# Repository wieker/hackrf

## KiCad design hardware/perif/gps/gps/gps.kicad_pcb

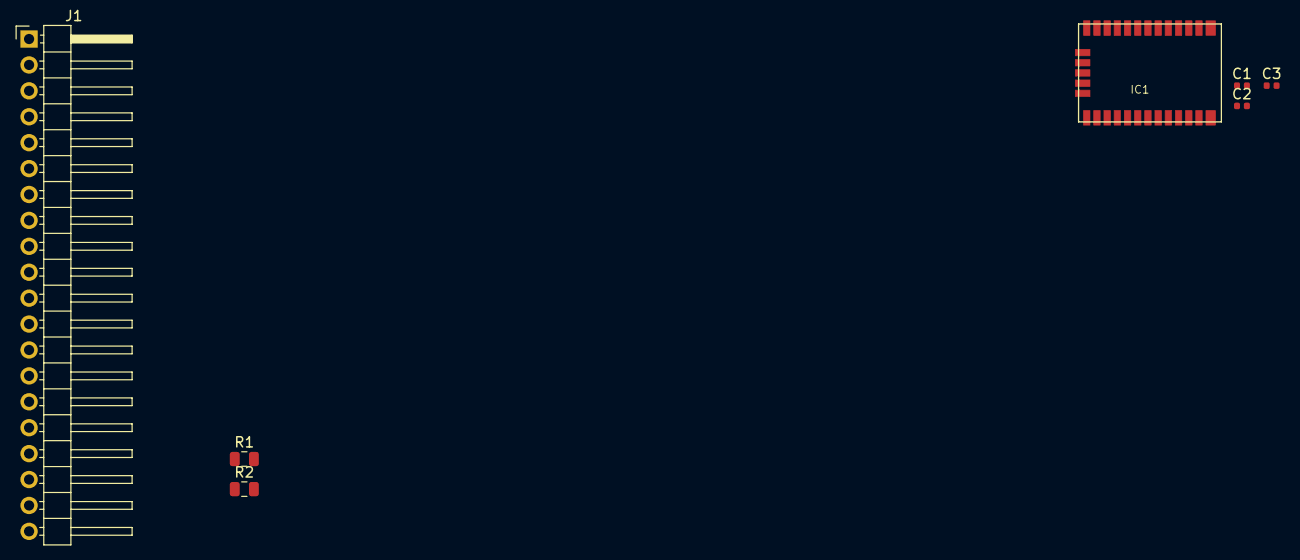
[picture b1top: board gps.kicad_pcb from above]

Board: 2 copper layers, 7 parts (0 on the bottom side), 7 nets, no tracks yet.

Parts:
C1, C2, C3: C; C_0402_1005Metric
IC1: CAM-M8Q
J1: Conn_01x20_Male; PinHeader_1x20_P2.54mm_Horizontal
R1, R2: 200; R_0805_2012Metric

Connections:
+3V3: C1.1, C2.1, C3.1, IC1.1, IC1.8, IC1.9, J1.19
GND: C1.2, C2.2, C3.2, IC1.4, IC1.5, IC1.10, IC1.11, IC1.12, IC1.13, IC1.14, IC1.15, IC1.18, IC1.19, IC1.21, IC1.22, IC1.27, IC1.31, J1.1, J1.4, J1.8, J1.15, J1.18, J1.20
unnamed: IC1.16, IC1.17
unnamed: IC1.25, R1.2
unnamed: IC1.26, R2.2
master_rx: J1.17, R1.1
master_tx: J1.16, R2.1

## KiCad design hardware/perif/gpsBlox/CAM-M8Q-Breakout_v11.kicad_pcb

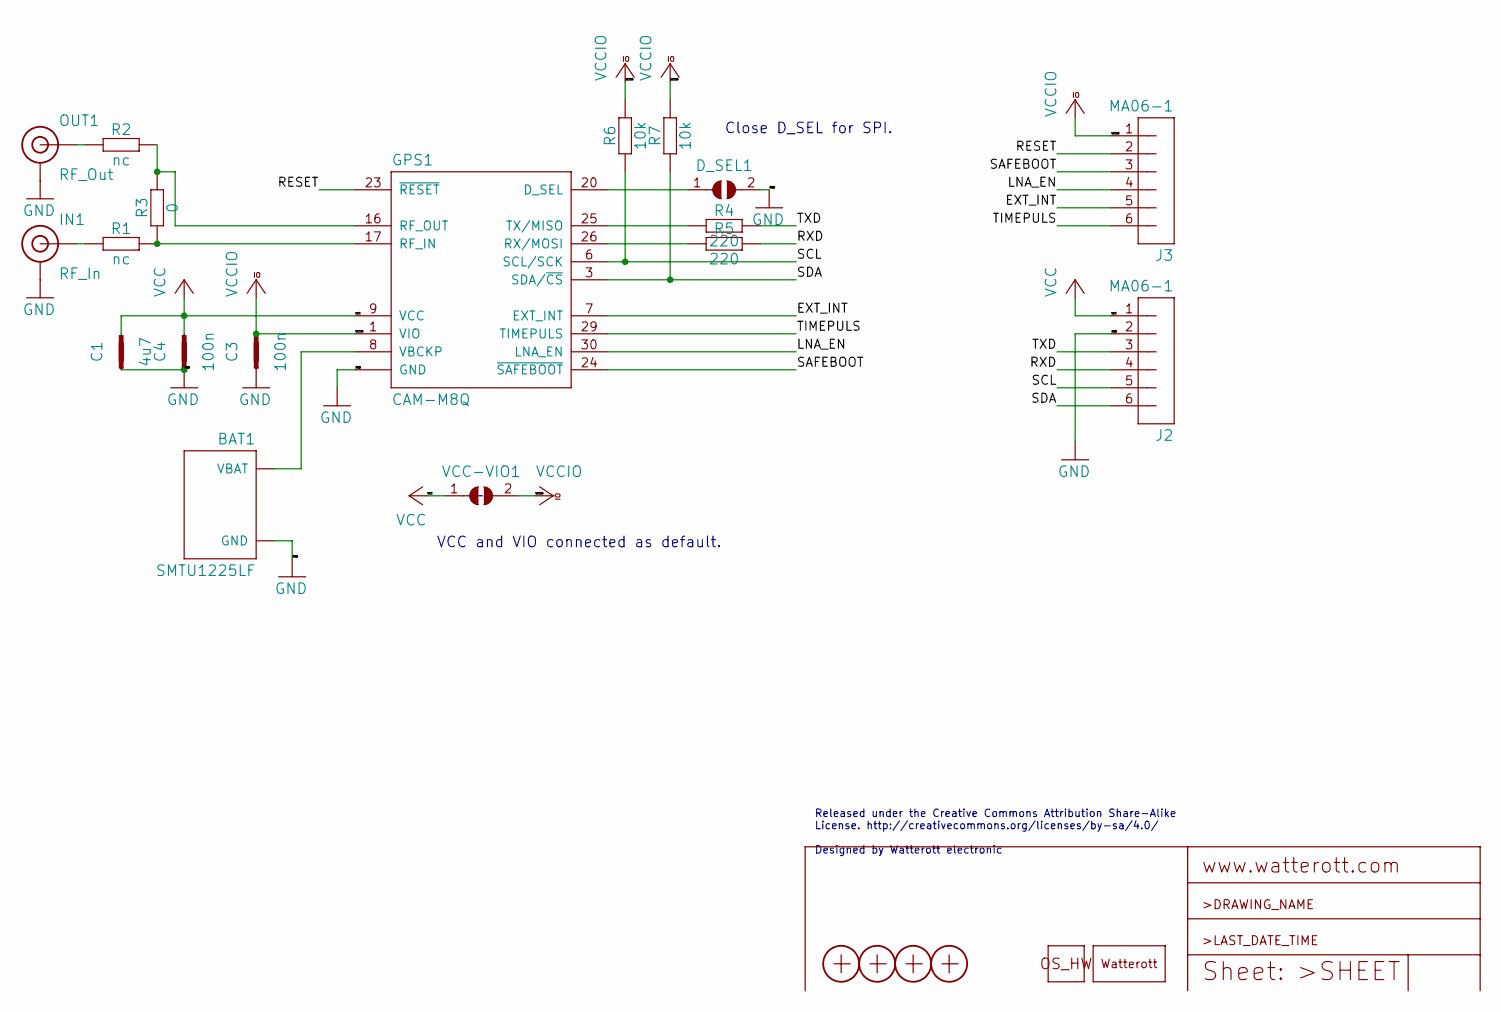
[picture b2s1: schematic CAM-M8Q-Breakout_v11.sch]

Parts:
BAT1: SMTU1225LF; BAT-SMTU1225LF
C1: 4u7; C0402
C3, C4: 100n; C0402
D_SEL1: JUMPER2-0603-NC; JUMPER2-0603_NC
GPS1: CAM-M8Q
IN1: RF_In; U.FL
J2, J3: MA06-1
LOGO3: LOGO_SPARK-4; SPARK_4MM
LOGO4: LOGO_OSHW-2; OSHW_2MM
OUT1: RF_Out; U.FL
R1, R2: nc; C0402
R3: 0; C0402
R4, R5: 220; C0402
R6, R7: 10k; C0402
VCC-VIO1: JUMPER2-0603-NC; JUMPER2-0603_NC
X1, X2, X3, X4: PASSER-07; PASSER_07MM

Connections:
/EXT_INT: GPS1.7 (EXT_INT), J3.5
/LNA_EN: GPS1.30 (LNA_EN), J3.4
/RESET: GPS1.23 (~RESET), J3.2
/RXD: J2.4, R5.2
/SAFEBOOT: GPS1.24 (~SAFEBOOT), J3.3
/SCL: GPS1.6 (SCL/SCK), J2.5, R6.1
/SDA: GPS1.3 (SDA/~CS), J2.6, R7.1
/TIMEPULS: GPS1.29 (TIMEPULS), J3.6
/TXD: J2.3, R4.2
GND: BAT1.- (GND), C1.1, C3.1, C4.1, D_SEL1.2, GPS1.4 (GND), GPS1.5 (GND), GPS1.10 (GND), GPS1.11 (GND), GPS1.12 (GND), GPS1.13 (GND), GPS1.14 (GND), GPS1.15 (GND), GPS1.18 (GND), GPS1.19 (GND), GPS1.21 (GND), GPS1.22 (GND), GPS1.27 (GND), GPS1.31 (GND), IN1.1 (GND), IN1.2 (GND), J2.2, OUT1.1 (GND), OUT1.2 (GND)
unnamed: BAT1.+ (VBAT), GPS1.8 (VBCKP)
unnamed: D_SEL1.1, GPS1.20 (D_SEL)
unnamed: GPS1.16 (RF_OUT), R2.2, R3.2
unnamed: GPS1.17 (RF_IN), R1.2, R3.1
unnamed: GPS1.25 (TX/MISO), R4.1
unnamed: GPS1.26 (RX/MOSI), R5.1
unnamed: IN1.FEED (SIGNAL), R1.1
unnamed: OUT1.FEED (SIGNAL), R2.1
VCC: C1.2, C4.2, GPS1.9 (VCC), J2.1, VCC-VIO1.1
VCCIO: C3.2, GPS1.1 (VIO), J3.1, R6.2, R7.2, VCC-VIO1.2

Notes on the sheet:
Released under the Creative Commons Attribution Share-Alike License. http://creativecommons.org/licenses/by-sa/4.0/ Designed by Watterott electronic
Close D_SEL for SPI.
VCC and VIO connected as default.

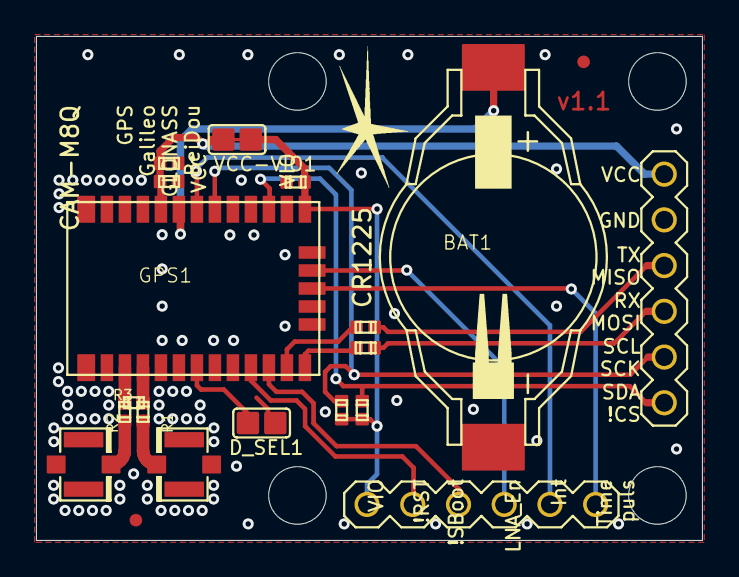
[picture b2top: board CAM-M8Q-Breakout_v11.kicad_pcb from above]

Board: 2 copper layers, 37.0 x 28.0 mm, 28 parts (0 on the bottom side), 20 nets.

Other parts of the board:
@HOLE0, @HOLE1, @HOLE2, @HOLE3: (no value)

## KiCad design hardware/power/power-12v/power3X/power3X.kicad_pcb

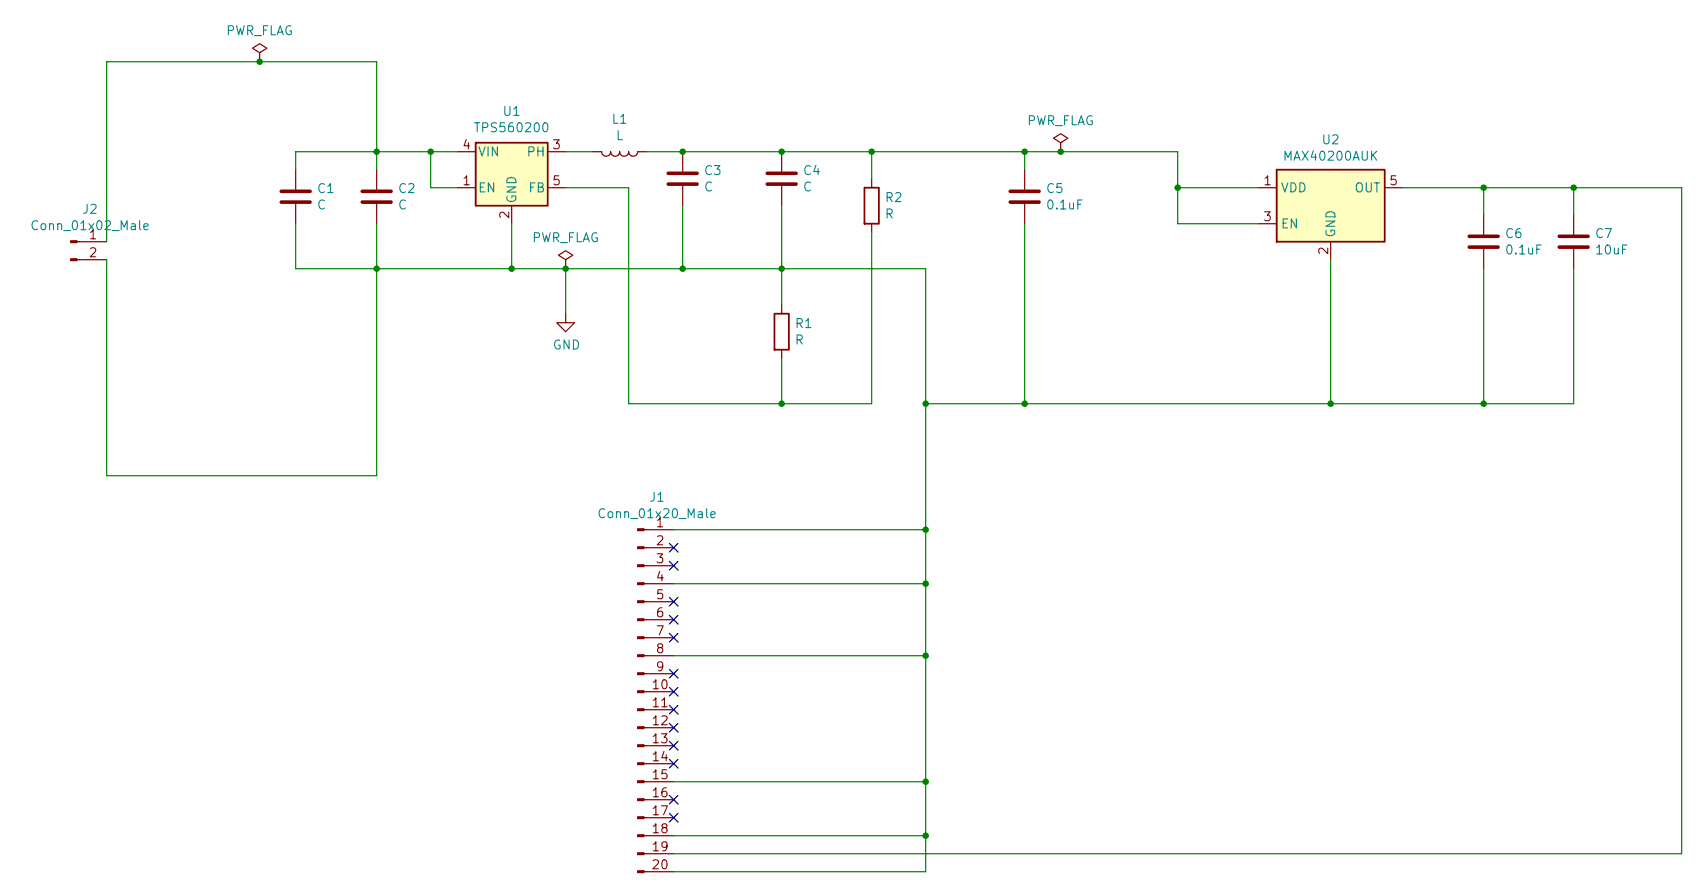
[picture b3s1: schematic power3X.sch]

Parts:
C1: C; C_0603_1608Metric
C2, C3, C4: C; C_0402_1005Metric
C5, C6: 0.1uF; C_0402_1005Metric
C7: 10uF; C_0402_1005Metric
J1: Conn_01x20_Male; PinHeader_1x20_P2.54mm_Horizontal
J2: Conn_01x02_Male; PinHeader_1x02_P2.54mm_Vertical
L1: L; L_0805_2012Metric
R1, R2: R; R_0402_1005Metric
U1: TPS560200; SOT-23-5
U2: MAX40200AUK; SOT-23-5

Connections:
GND: C1.2, C2.2, C3.2, C4.2, C5.2, C6.2, C7.2, J1.1, J1.4, J1.8, J1.15, J1.18, J1.20, J2.2, R1.1, U1.2 (GND), U2.2 (GND)
unnamed: C1.1, C2.1, J2.1, U1.1 (EN), U1.4 (VIN)
unnamed: C3.1, C4.1, C5.1, L1.1, R2.1, U2.1 (VDD), U2.3 (EN)
unnamed: C6.1, C7.1, J1.19, U2.5 (OUT)
unnamed: L1.2, U1.3 (PH)
unnamed: R1.2, R2.2, U1.5 (FB)

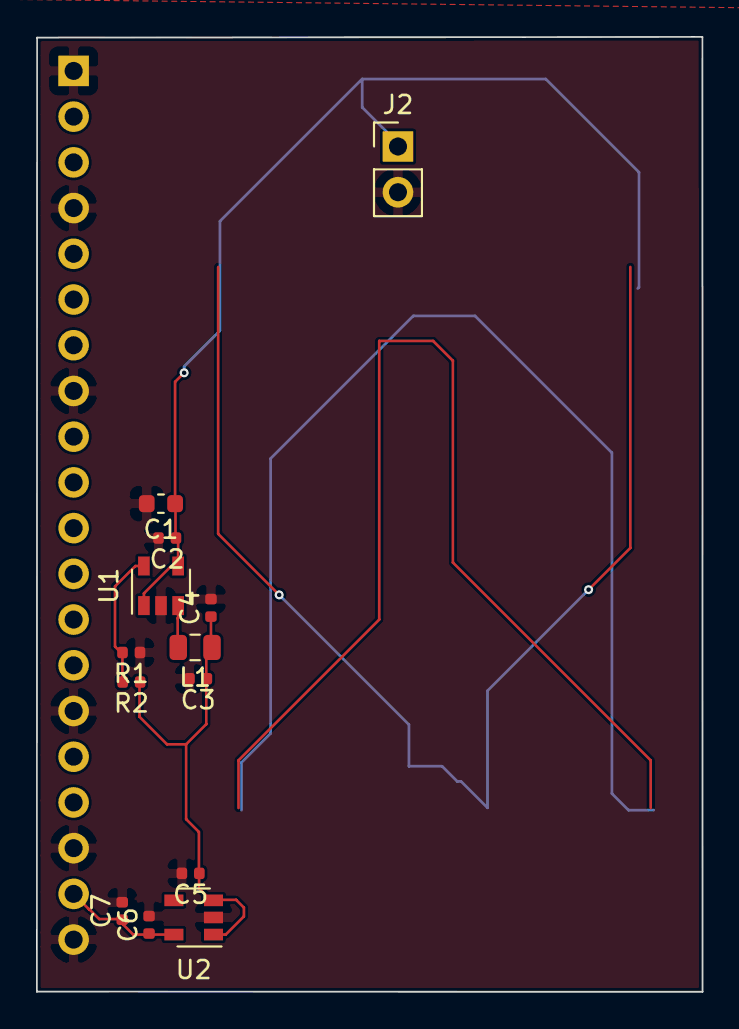
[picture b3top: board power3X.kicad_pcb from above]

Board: 2 copper layers, 37.0 x 53.0 mm, 14 parts (1 on the bottom side), 6 nets.

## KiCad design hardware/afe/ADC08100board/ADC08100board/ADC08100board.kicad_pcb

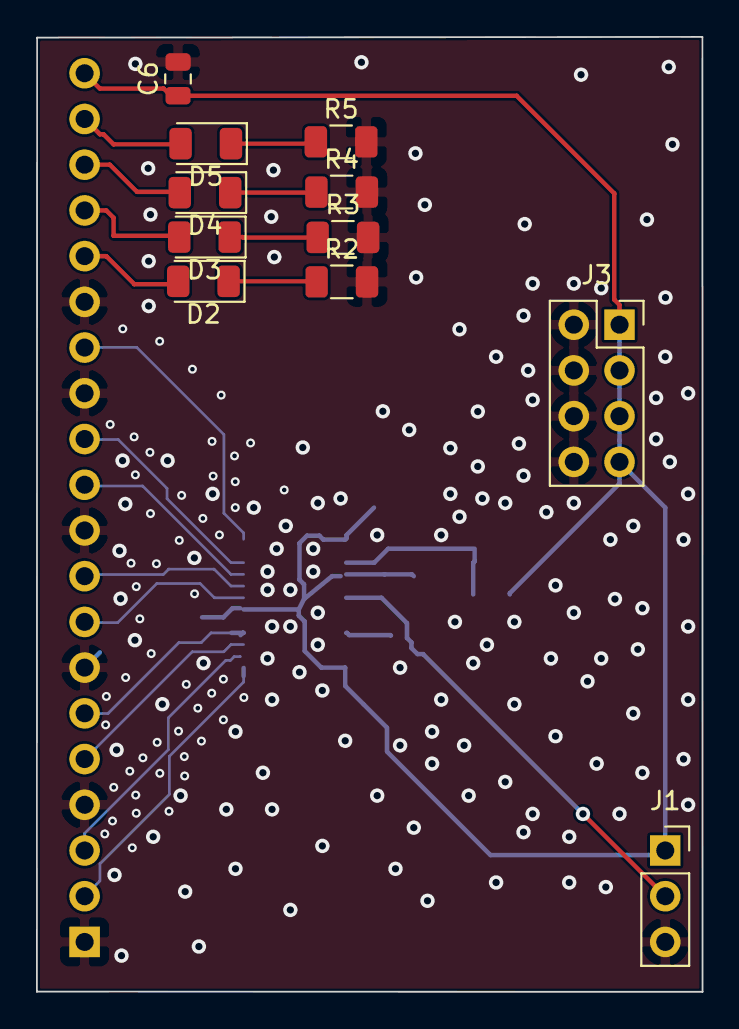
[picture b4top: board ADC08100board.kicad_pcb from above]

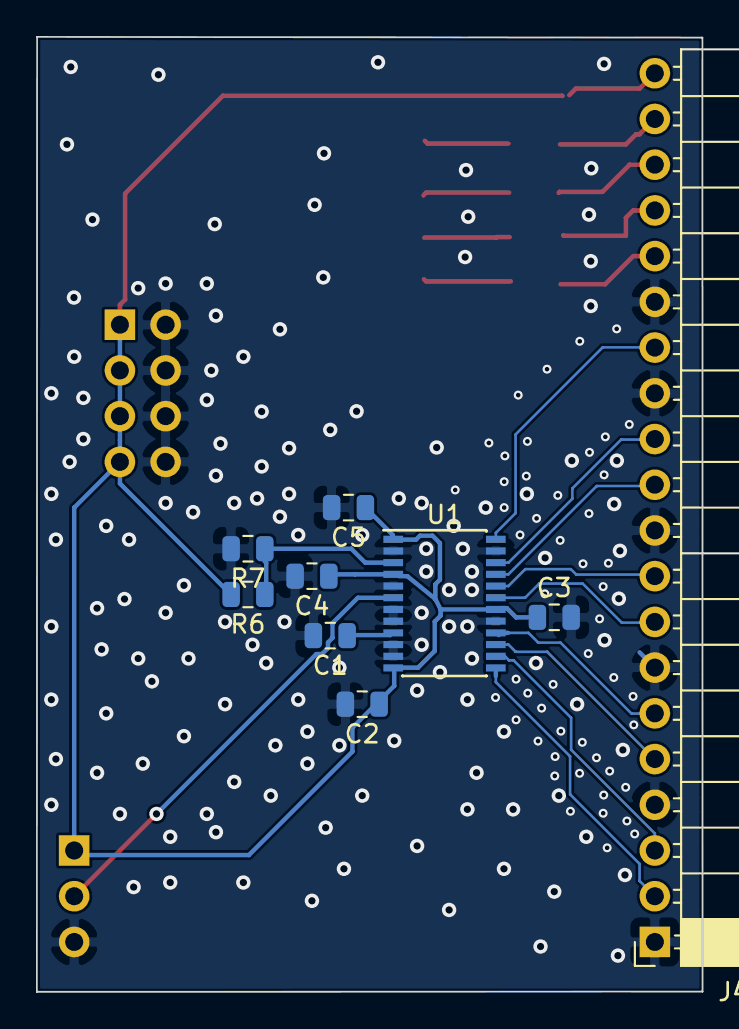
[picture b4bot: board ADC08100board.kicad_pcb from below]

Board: 2 copper layers, 37.0 x 53.0 mm, 20 parts (9 on the bottom side), 22 nets.

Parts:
C1, C2, C3, C4, C5, C6: 0.1uF; C_0805_2012Metric
D2, D3, D4, D5: LED; LED_1206_3216Metric
J1: Conn_01x03_Male; PinSocket_1x03_P2.54mm_Vertical
J3: Conn_02x04_Odd_Even; PinSocket_2x04_P2.54mm_Vertical
J4: Conn_01x20_Female; PinSocket_1x20_P2.54mm_Horizontal
R2, R3, R4, R5: 10 kOhm; R_1206_3216Metric
R6: 200Ohm; R_0805_2012Metric
R7: 100Ohm; R_0805_2012Metric
U1: ADC08060; TSSOP-24_4.4x7.8mm_P0.65mm

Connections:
+3V3: C2.1, C3.1, C4.1, C5.1, C6.1, J1.1, J3.1, J3.3, J3.5, J3.7, J4.20, R6.2, U1.1, U1.4, U1.12, U1.18
GND: C1.2, C2.2, C3.2, C4.2, C5.2, C6.2, J1.3, J3.2, J3.4, J3.6, J3.8, J4.1, J4.4, J4.7, J4.10, J4.13, J4.15, R2.2, R3.2, R4.2, R5.2, R7.2, U1.2, U1.5, U1.7, U1.8, U1.10, U1.11, U1.17, U1.23
unnamed: C1.1, U1.9
unnamed: D2.1, R2.1
unnamed: D2.2, J4.16
unnamed: D3.1, R3.1
unnamed: D3.2, J4.17
unnamed: D4.1, R4.1
unnamed: D4.2, J4.18
unnamed: D5.1, R5.1
unnamed: D5.2, J4.19
unnamed: J1.2, U1.6
unnamed: J4.2, U1.13
unnamed: J4.3, U1.14
unnamed: J4.5, U1.15
unnamed: J4.6, U1.16
unnamed: J4.8, U1.19
unnamed: J4.9, U1.20
unnamed: J4.11, U1.21
unnamed: J4.12, U1.22
unnamed: J4.14, U1.24
unnamed: R6.1, R7.1, U1.3

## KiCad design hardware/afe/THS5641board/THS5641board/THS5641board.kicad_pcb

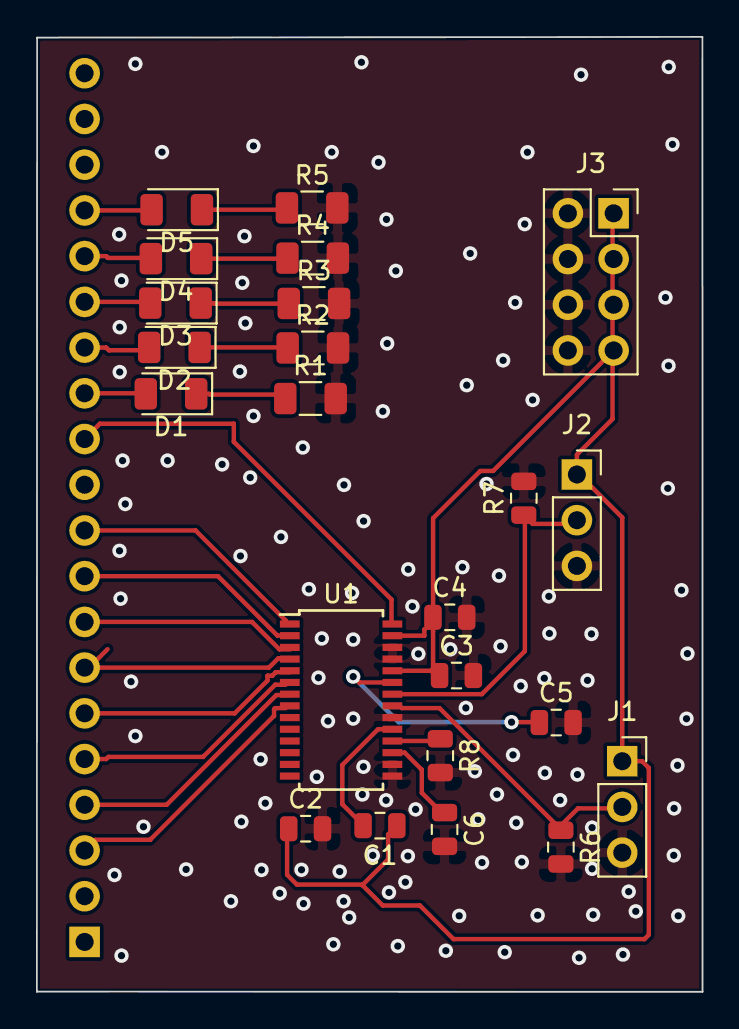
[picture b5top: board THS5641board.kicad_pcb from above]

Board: 2 copper layers, 37.0 x 53.0 mm, 24 parts (1 on the bottom side), 27 nets.

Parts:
C1, C2, C3, C4, C5, C6: 0.1uF; C_0805_2012Metric
D1, D2, D3, D4, D5: LED; LED_1206_3216Metric
J1, J2: Conn_01x03_Male; PinSocket_1x03_P2.54mm_Vertical
J3: Conn_02x04_Odd_Even; PinSocket_2x04_P2.54mm_Vertical
J4: Conn_01x20_Female; PinSocket_1x20_P2.54mm_Horizontal
R1, R2, R3, R4, R5: 10 kOhm; R_1206_3216Metric
R6, R7: 50Ohm; R_0805_2012Metric
R8: 2kOhm; R_0805_2012Metric
U1: THS5641; TSSOP-28_4.4x9.7mm_P0.65mm

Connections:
+3V3: C1.1, C2.1, C3.1, C4.1, J1.1, J2.1, J3.1, J3.3, J3.5, J3.7, U1.24, U1.27
GND: C2.2, C3.2, C4.2, C5.2, C6.2, J1.3, J2.3, J3.2, J3.4, J3.6, J3.8, R1.2, R2.2, R3.2, R4.2, R5.2, R6.2, R7.2, R8.2, U1.15, U1.16, U1.20, U1.25, U1.26
unnamed: C1.2, U1.19
unnamed: C5.1, U1.23
unnamed: C6.1, U1.17
unnamed: D1.1, R1.1
unnamed: D1.2, J4.13
unnamed: D2.1, R2.1
unnamed: D2.2, J4.14
unnamed: D3.1, R3.1
unnamed: D3.2, J4.15
unnamed: D4.1, R4.1
unnamed: D4.2, J4.16
unnamed: D5.1, R5.1
unnamed: D5.2, J4.17
unnamed: J1.2, R6.1, U1.21
unnamed: J2.2, R7.1, U1.22
unnamed: J4.3, U1.8
unnamed: J4.4, U1.7
unnamed: J4.5, U1.6
unnamed: J4.6, U1.5
unnamed: J4.7, U1.4
unnamed: J4.8, U1.3
unnamed: J4.9, U1.2
unnamed: J4.10, U1.1
unnamed: J4.12, U1.28
unnamed: R8.1, U1.18

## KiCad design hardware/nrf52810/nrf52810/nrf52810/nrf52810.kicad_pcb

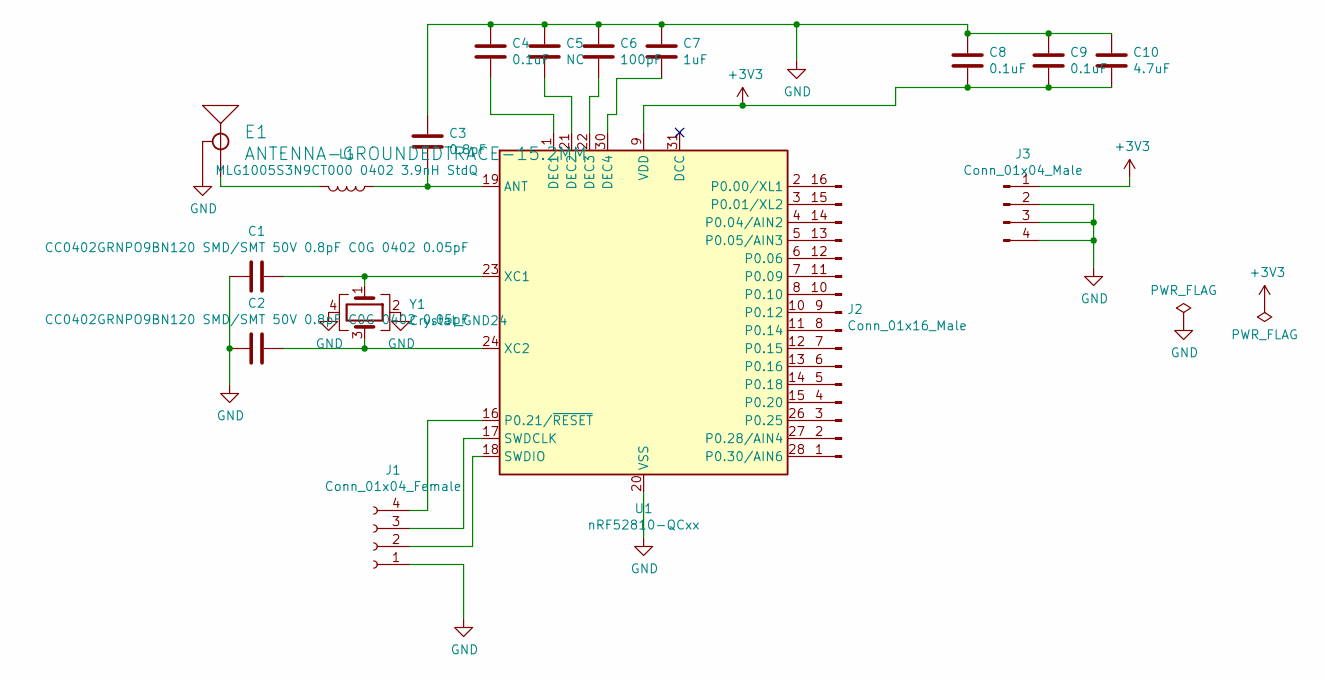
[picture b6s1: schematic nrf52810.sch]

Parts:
C1, C2: CC0402GRNPO9BN120 SMD/SMT 50V 0.8pF C0G 0402 0.05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; C_0402_1005Metric
C3: 0.8pF; C_0402_1005Metric
C4, C8, C9: 0.1uF; C_0402_1005Metric
C5: NC; C_0402_1005Metric
C6: 100pF; C_0402_1005Metric
C7: 1uF; C_1206_3216Metric
C10: 4.7uF; C_1206_3216Metric
E1: ANTENNA-GROUNDEDTRACE-15.2MM; TRACE_ANTENNA_2.4GHZ_15.2MM
J1: Conn_01x04_Female; PinHeader_1x04_P2.54mm_Vertical
J2: Conn_01x16_Male; PinHeader_1x16_P2.54mm_Vertical
J3: Conn_01x04_Male; PinHeader_1x04_P2.54mm_Vertical
L1: MLG1005S3N9CT000 0402 3.9nH StdQ; L_0402_1005Metric
U1: nRF52810-QCxx; QFN-32-1EP_5x5mm_P0.5mm_EP3.6x3.6mm
Y1: Crystal_GND24; Crystal_SMD_3225-4Pin_3.2x2.5mm

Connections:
+3V3: C8.2, C9.2, C10.2, J3.1, U1.9 (VDD), U1.25 (VDD), U1.32 (VDD)
GND: C1.2, C2.2, C3.1, C4.1, C5.1, C6.1, C7.1, C8.1, C9.1, C10.1, E1.GND, J1.1, J3.2, J3.3, J3.4, U1.20 (VSS), U1.29 (VSS), U1.33 (VSS), Y1.2, Y1.4
unnamed: C1.1, U1.23 (XC1), Y1.1
unnamed: C2.1, U1.24 (XC2), Y1.3
unnamed: C3.2, L1.1, U1.19 (ANT)
unnamed: C4.2, U1.1 (DEC1)
unnamed: C5.2, U1.21 (DEC2)
unnamed: C6.2, U1.22 (DEC3)
unnamed: C7.2, U1.30 (DEC4)
unnamed: E1.ANT (SIGNAL), L1.2
unnamed: J1.2, U1.18 (SWDIO)
unnamed: J1.3, U1.17 (SWDCLK)
unnamed: J1.4, U1.16 (P0.21/~RESET)
unnamed: J2.1, U1.28 (P0.30/AIN6)
unnamed: J2.2, U1.27 (P0.28/AIN4)
unnamed: J2.3, U1.26 (P0.25)
unnamed: J2.4, U1.15 (P0.20)
unnamed: J2.5, U1.14 (P0.18)
unnamed: J2.6, U1.13 (P0.16)
unnamed: J2.7, U1.12 (P0.15)
unnamed: J2.8, U1.11 (P0.14)
unnamed: J2.9, U1.10 (P0.12)
unnamed: J2.10, U1.8 (P0.10)
unnamed: J2.11, U1.7 (P0.09)
unnamed: J2.12, U1.6 (P0.06)
unnamed: J2.13, U1.5 (P0.05/AIN3)
unnamed: J2.14, U1.4 (P0.04/AIN2)
unnamed: J2.15, U1.3 (P0.01/XL2)
unnamed: J2.16, U1.2 (P0.00/XL1)

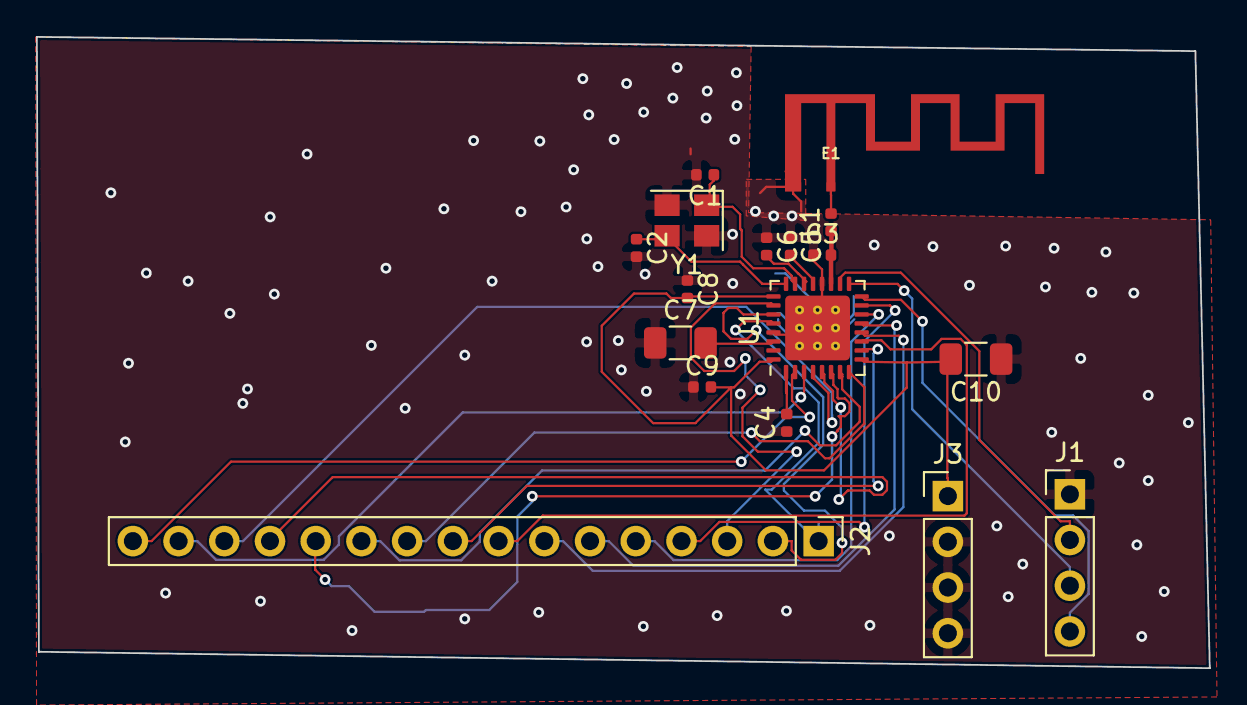
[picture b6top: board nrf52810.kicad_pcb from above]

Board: 2 copper layers, 65.2 x 35.1 mm, 17 parts (0 on the bottom side), 29 nets.

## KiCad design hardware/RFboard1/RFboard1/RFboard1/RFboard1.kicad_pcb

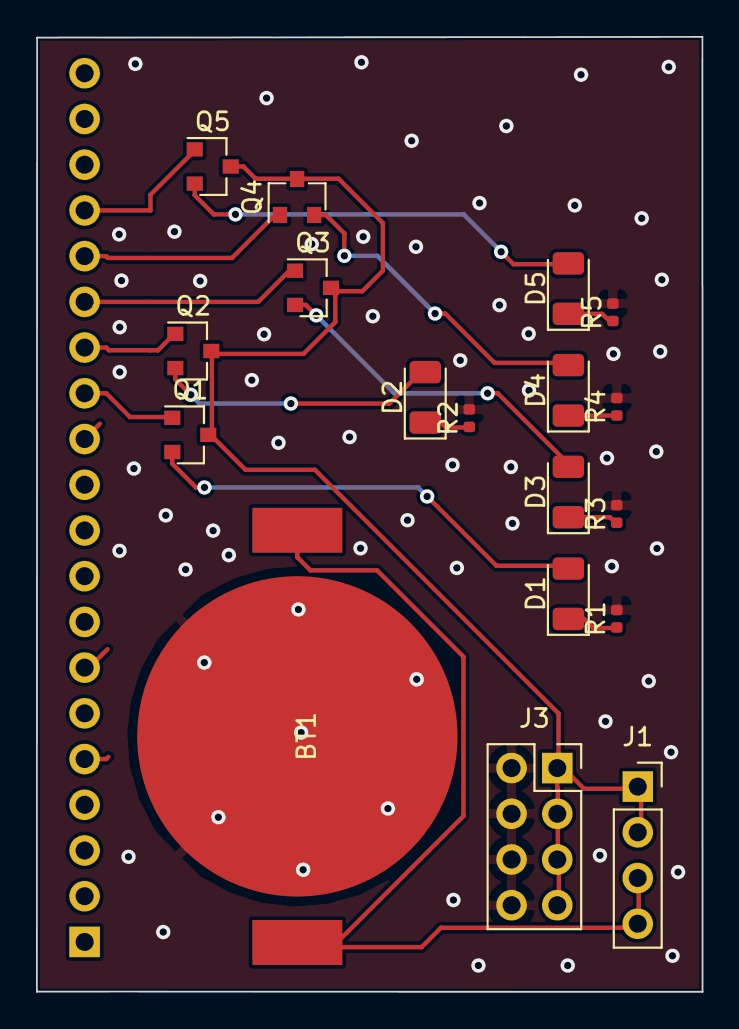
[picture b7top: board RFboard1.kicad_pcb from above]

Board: 2 copper layers, 37.0 x 53.0 mm, 19 parts (1 on the bottom side), 18 nets.

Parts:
BT1: Battery_Cell; CR2032
D1, D2, D3, D4, D5: LED; LED_1206_3216Metric
J1: Conn_01x04_Male; PinSocket_1x04_P2.54mm_Vertical
J3: Conn_02x04_Odd_Even; PinSocket_2x04_P2.54mm_Vertical
J4: Conn_01x20_Female; PinSocket_1x20_P2.54mm_Horizontal
Q1, Q2, Q3, Q4, Q5: 2N7002; SOT-23
R1, R2, R3, R4, R5: 10 kOhm; R_0402_1005Metric

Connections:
+3V3: J1.1, J1.2, J3.1, J3.3, J3.5, J3.7, Q1.3, Q2.3, Q3.3, Q4.3, Q5.3
GND: BT1.2, J3.2, J3.4, J3.6, J3.8, R1.2, R2.2, R3.2, R4.2, R5.2
unnamed: BT1.1, J1.3, J1.4
unnamed: D1.1, R1.1
unnamed: D1.2, Q1.2
unnamed: D2.1, R2.1
unnamed: D2.2, Q2.2
unnamed: D3.1, R3.1
unnamed: D3.2, Q3.2
unnamed: D4.1, R4.1
unnamed: D4.2, Q4.2
unnamed: D5.1, R5.1
unnamed: D5.2, Q5.2
unnamed: J4.13, Q1.1
unnamed: J4.14, Q2.1
unnamed: J4.15, Q3.1
unnamed: J4.16, Q4.1
unnamed: J4.17, Q5.1

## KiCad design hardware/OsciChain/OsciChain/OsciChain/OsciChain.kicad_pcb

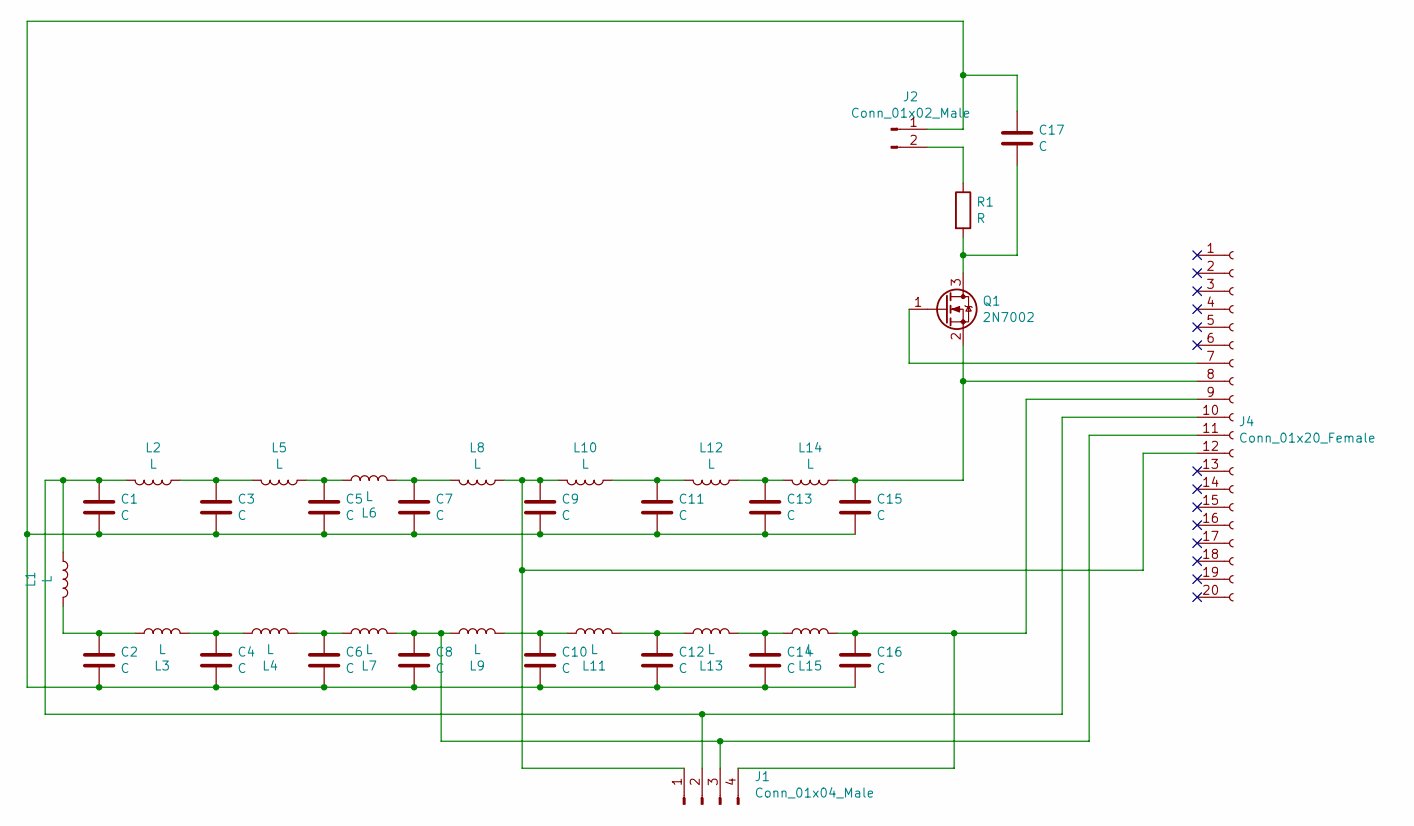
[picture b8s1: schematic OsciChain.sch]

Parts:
C1, C2, C3, C4, C5, C6, C7, C8, C9, C10, C11, C12, C13, C14, C15, C16, C17: C; C_Radial_D16.0mm_H25.0mm_P7.50mm
J1: Conn_01x04_Male; PinSocket_1x04_P2.54mm_Vertical
J2: Conn_01x02_Male; PinSocket_1x02_P2.54mm_Vertical
J4: Conn_01x20_Female; PinSocket_1x20_P2.54mm_Horizontal
L1, L2, L3, L4, L5, L6, L7, L8, L9, L10, L11, L12, L13, L14, L15: L; L_Radial_D6.0mm_P4.00mm
Q1: 2N7002; SOT-23
R1: R; R_Axial_DIN0414_L11.9mm_D4.5mm_P20.32mm_Horizontal

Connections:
unnamed: C1.1, J1.2, J4.10, L1.1, L2.2
unnamed: C1.2, C2.2, C3.2, C4.2, C5.2, C6.2, C7.2, C8.2, C9.2, C10.2, C11.2, C12.2, C13.2, C14.2, C15.2, C16.2, C17.1, J2.1
unnamed: C2.1, L1.2, L3.1
unnamed: C3.1, L2.1, L5.2
unnamed: C4.1, L3.2, L4.1
unnamed: C5.1, L5.1, L6.1
unnamed: C6.1, L4.2, L7.1
unnamed: C7.1, L6.2, L8.2
unnamed: C8.1, J1.3, J4.11, L7.2, L9.1
unnamed: C9.1, J1.1, J4.12, L8.1, L10.2
unnamed: C10.1, L9.2, L11.1
unnamed: C11.1, L10.1, L12.2
unnamed: C12.1, L11.2, L13.1
unnamed: C13.1, L12.1, L14.2
unnamed: C14.1, L13.2, L15.1
unnamed: C15.1, J4.8, L14.1, Q1.2 (S)
unnamed: C16.1, J1.4, J4.9, L15.2
unnamed: C17.2, Q1.3 (D), R1.2
unnamed: J2.2, R1.1
unnamed: J4.7, Q1.1 (G)

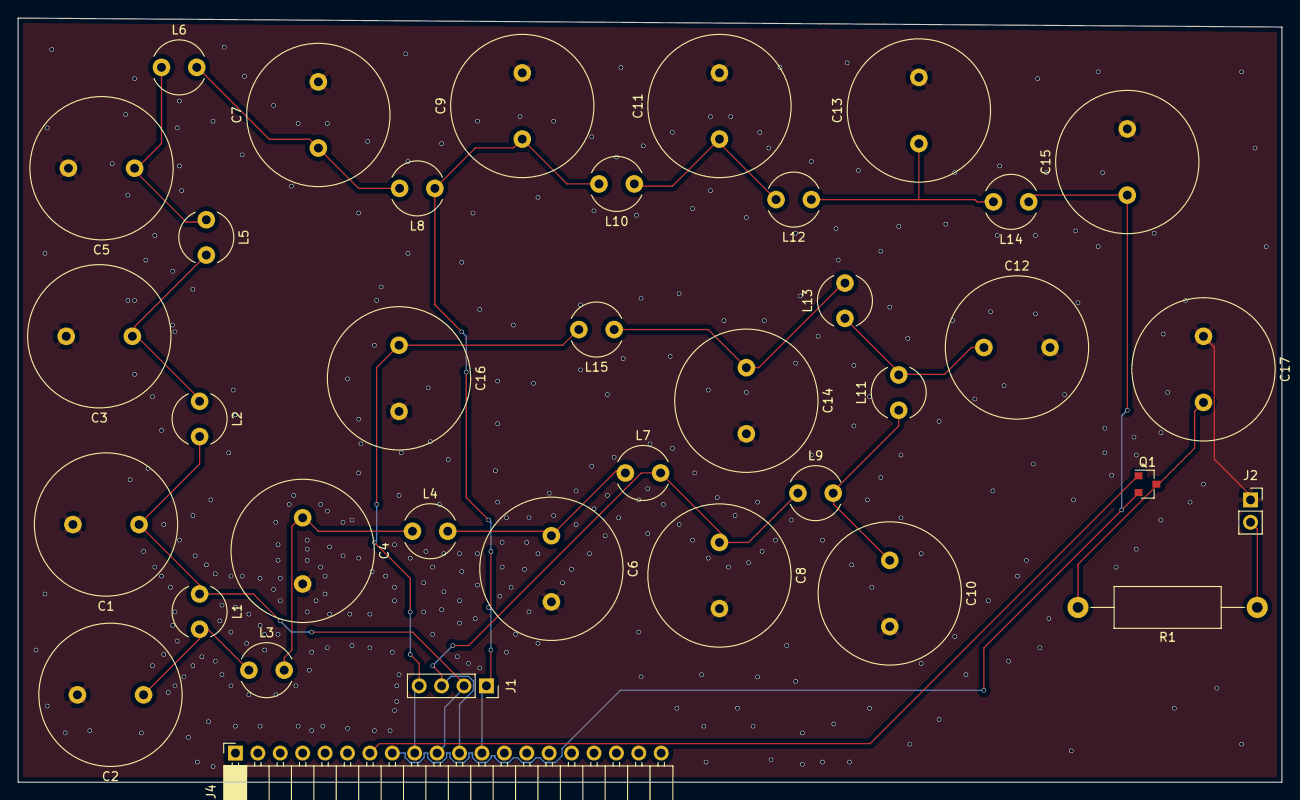
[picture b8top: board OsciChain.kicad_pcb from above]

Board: 2 copper layers, 143.3 x 86.6 mm, 37 parts (0 on the bottom side), 20 nets.

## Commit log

2019-05-17 redesign
2019-05-18 blink on OM13088UL board
2019-06-04 CLion files + generated CMake files
2019-06-04 enumerated as an USB device on the LPCXpresso LPC4367 OM13088UL board
2019-06-05 LPCXpresso LPC4367 OM13088UL board software reset on request
2019-06-09 LPCXpresso LPC4367 OM13088UL board openocd.cfg with disabled M0 to flash images withing integrated debugger
2019-06-09 LPCXpresso LPC4367 OM13088UL OpenOCD flash image command
2019-06-09 LPCXpresso LPC4367 OM13088UL memory map correction
2019-06-09 LPCXpresso LPC4367 OM13088UL USB comm Part I
2019-06-10 read from USB
2019-06-10 LPCXpresso LPC4367 OM13088UL: fixed hang
2019-06-11 LPCXpresso LPC4367 OM13088UL: first I2C experiments
2019-06-19 LPCXpresso LPC4367 OM13088UL: starting to port I2C example from the LPCopen library
2019-06-19 LPCXpresso LPC4367 OM13088UL: starting to port I2C example from the LPCopen library: working I/O
2019-06-20 LPCXpresso LPC4367 OM13088UL: scan of the I2C buf of the X-NUCLEO-NFC04A1 NFC board
2019-06-20 LPCXpresso LPC4367 OM13088UL: I2C isr
2019-06-20 LPCXpresso LPC4367 OM13088UL: I2C debug 1
2019-06-20 LPCXpresso LPC4367 OM13088UL: I2C scan in interrupt mode
2019-06-25 LPCXpresso LPC4367 OM13088UL: I2C read register of the ST25DV04K
2019-06-26 LPCXpresso LPC4367 OM13088UL: dump the I2C NFC tag ST25DV04K
2019-06-27 LPCXpresso LPC4367 OM13088UL: I2C <=> USB read I
2019-07-19 LPCXpresso LPC4367 OM13088UL: Si5351 IO
2019-07-20 LPCXpresso LPC4367 OM13088UL: ADC example
2019-07-20 LPCXpresso LPC4367 OM13088UL: ADC isr
2019-07-20 LPCXpresso LPC4367 OM13088UL: timers
2019-07-20 LPCXpresso LPC4367 OM13088UL: ADC on timer Part I
2019-07-20 LPCXpresso LPC4367 OM13088UL: ADC on timer Part II
2019-07-20 LPCXpresso LPC4367 OM13088UL: Timer => GIMA => ADC trigger
2019-07-20 LPCXpresso LPC4367 OM13088UL: I2C r/w of the Si5351 Multisynth NA Parameters
2019-07-20 LPCXpresso LPC4367 OM13088UL: counter for external pin
2019-07-20 LPCXpresso LPC4367 OM13088UL: si5351 clock source is started
2019-07-20 LPCXpresso LPC4367 OM13088UL: si5351 clock source settings + counter
2019-07-20 LPCXpresso LPC4367 OM13088UL: si5351 clock source auto shutdown
2019-07-20 LPCXpresso LPC4367 OM13088UL: si5351 clock source configuration improvements
2019-07-23 board for OM13088UL started
2019-07-24 board for OM13088UL started-2
2019-07-24 board for OM13088UL started library
2019-07-25 board for OM13088UL: ST25DV04K symbol
2019-07-26 board for OM13088UL: process 1
2019-07-27 board for OM13088UL: process 2
2019-07-27 board for OM13088UL: process 3
2019-07-27 board for OM13088UL: process 4
2019-07-27 board for OM13088UL: process 5
2019-07-27 board for OM13088UL: process 6
2019-07-27 board for OM13088UL: fixed SCL/SDA issue
2019-08-04 EEPROMboard
2019-08-05 alpha and eeprom boards
2019-08-06 LPCXpresso LPC4367 OM13088UL: ADC settings
2019-08-10 default 2 layer
2019-08-10 NCP LPC61u68 board
2019-08-10 NXP LPC61u68 board
2019-08-10 started boards
2019-08-10 NXP LPC51u68: added regulator
2019-08-11 NXP LPC51u68 more
2019-08-11 NXP LPC51u68 layout I
2019-08-11 NXP LPC51u68 layout II
2019-08-11 NXP LPC51u68 layout III
2019-08-11 NXP LPC51u68 gerbers I
2019-08-11 ice40 board
2019-08-11 first gerber for ice40 board
2019-08-12 LPCXpresso LPC4367 OM13088UL: trying SPI
2019-08-20 LPCXpresso LPC4367 OM13088UL: trying SPI: blocking
2019-08-21 LPCXpresso LPC4367 OM13088UL: trying SPI: SSP between boards
2019-08-24 LPCXpresso LPC4367 OM13088UL: trying SPI: SSP between boards: debug
2019-08-24 LPCXpresso LPC4367 OM13088UL: trying SPI: SPI Flash execute commands
2019-08-25 LPCXpresso LPC4367 OM13088UL: trying SPI: SPI master/slave selection
2019-08-25 LPCXpresso LPC4367 OM13088UL: SGPIO isr
2019-08-25 LPCXpresso LPC4367 OM13088UL: SGPIO isr: self-concatenation
2019-08-26 LPCXpresso LPC4367 OM13088UL: SGPIO isr: self-concatenation sync
2019-08-26 LPCXpresso LPC4367 OM13088UL: SGPIO isr: direct-read
2019-08-26 LPCXpresso LPC4367 OM13088UL: SGPIO: read slow speed SPI (endian issue? speed issue?)
2019-08-26 LPCXpresso LPC4367 OM13088UL: SGPIO: read slow speed SPI (endian issue? speed optmimization)
2019-08-26 LPCXpresso LPC4367 OM13088UL: SGPIO: read slow speed SPI correct endian
2019-08-26 LPCXpresso LPC4367 OM13088UL: SGPIO: SPI CS# as qualifier
2019-08-27 LPC54u I2C ISP test 1
2019-08-27 LPC51u ADC test
2019-08-27 i2C test
2019-08-29 starting fpga code
2019-08-30 SRAMboard I
2019-08-31 regenerated lpc51u68board with correct solder mask
2019-09-01 SRAMboardBGA
2019-09-01 SRAMboardBGA: version for OSHPARK
2019-09-01 FIXED solder mask issue
2019-09-01 Started SGPIO => FPGA
2019-09-01 Started SGPIO => FPGA. I/O
2019-09-02 Improvements
2019-09-03 Working LPC51u ISP I2C probe
2019-09-03 Working LPC51u ISP I2C version command
2019-09-05 SPI flash readID
2019-09-05 sigio ice40 SPI
2019-09-05 FPGA SPI mirror
2019-09-06 timer counter for CS#
2019-09-07 FPGA => LPC clk counter
2019-09-07 SGPIO => FPGA Debug I
2019-09-07 SGPIO => FPGA Debug II
2019-09-07 SGPIO: read correct "iceprog -ts" SPI comm with 2-bit shift
2019-09-07 SGPIO: read correct "iceprog -ts" SPI comm without 2-bit shift and with 20-byte ID
2019-09-08 const out
2019-09-08 Verilog shift register
2019-09-08 SRAMboardTSSOP28
2019-09-08 FPGA counter
2019-09-08 FPGA counter: fixed initial issue
2019-09-08 FPGA counter: stripes
2019-09-08 FPGA counter: one
2019-09-08 FPGA counter: CS#
2019-09-10 started UART
2019-09-13 UART comm works
2019-09-14 UART int
2019-09-14 UART int 2
2019-09-14 UART xcvr
2019-09-14 Started PicoSOC FPGA debug
2019-09-14 Experiments with FPGA SPI
2019-09-14 Read SPI flash ID with FPGA
2019-09-14 Fixed ice40up5 flash access from LPC board
2019-09-14 experiments with ice40brk SPI flash access from LPC
2019-09-16 first SRAM
2019-09-20 LPC => SRAM interface works
2019-09-21 ice40HX1K-TQFP144 code
2019-09-21 Programming iCE40-1KHX EVB through ice40UP5K EVB (pass SCK line)
2019-09-22 LPC => iCE40-1KHX EVB SPI access with CDONE
2019-09-22 LPC => iCE40-1KHX EVB SPI access with CDONE: spi read
2019-09-22 LPC => iCE40-1KHX EVB SPI access with CDONE: spi read the same as binary firmware
2019-09-23 LPC => iCE40-1KHX EVB SPI access: minor refactoring
2019-09-23 LPC => iCE40-1KHX EVB SPI access: USB access
2019-09-24 LPC => iCE40-1KHX EVB SPI access: dump SPI through USB
2019-09-27 LPC => iCE40-1KHX EVB SPI access: USB write
2019-09-28 LPC => iCE40-1KHX EVB SPI access: some refactoring
2019-09-28 LPC => iCE40-1KHX EVB SPI access: Read random addresses from host
2019-09-28 LPC => iCE40-1KHX EVB SPI access: started dump
2019-09-28 LPC => iCE40-1KHX EVB SPI access: dump identical ice40HX1K firmware
2019-09-28 LPC => iCE40-1KHX EVB SPI access: Write Enable command works
2019-09-28 LPC => iCE40-1KHX EVB SPI access: ERASE command works
2019-09-28 LPC => iCE40-1KHX EVB SPI access: ice40HX1K programmer PoC
2019-09-28 started ice40HX1K board
2019-09-28 ice40HX1K board: SPI programmer
2019-09-29 ice40HX1K board: board without SRAM/ADC
2019-10-01 HX1Kboard improvement
2019-10-02 updated PCB settings
2019-10-10 ice40HX1K board: board assembled and tested. it works
2019-10-10 ice40HX1K board: next iteration
2019-10-11 ice40HX1K board: SPI wakeup
2019-10-11 ice40HX1K board: ring oscillator
2019-10-12 ice40HX1K + SRAM board
2019-10-12 AD9283 board
2019-10-17 hx1k-6502 initial
2019-10-17 hx1k-6502 at least it blinks...
2019-10-17 hx1k-6502 slow blink with C program
2019-10-19 hx1k-6502 for HX1KADC board
2019-10-19 HX1KADC board: SRAM
2019-10-19 HX1KADC board: blink
2019-10-19 HX1KADC board: SRAM I/O
2019-10-20 HX1KADC board: 6502 => SRAM some blinks
2019-10-20 HX1KADC board: 6502 => SRAM some blinks with ROM
2019-10-20 HX1KADC board: 6502 => SRAM blink CS
2019-10-20 HX1KADC board: 6502 => SRAM blink from C
2019-10-20 HX1KADC board: 6502 => SRAM blink experiments
2019-10-20 HX1KADC board: started UART
2019-10-20 HX1KADC board: found clock estimate/ Near 3.2 MHz for 200 LUT delay
2019-10-20 HX1KADC board: UART TX/RX
2019-10-20 HX1KADC board: UART ctl
2019-10-20 HX1KADC board: MCPU
2019-10-20 HX1KADC board: 6502 works again
2019-10-20 HX1KADC board: 6502 UART works
2019-10-20 HX1KADC board: 6502 SRAM I
2019-10-20 HX1KADC board: 6502 SRAM II
2019-10-20 HX1KADC board: 6502 => SRAM works
2019-10-21 HX1KADC board: 6502 => SRAM 1 byte I/O
2019-10-21 HX1KADC board: 6502 => SRAM registered I/O
2019-10-21 HX1KADC board: 6502 => SRAM registered I/O implemented
2019-10-21 HX1KADC board: 6502 => SRAM 30 MHz + UART + GPIO
2019-10-23 started ice40LP1K-CM36 board
2019-10-23 started capSense board
2019-10-25 LP1K + HX1Kcap boards
2019-10-26 ice40 HX1K: first ADC AD9288 suport firmware
2019-10-26 ice40 HX1K: adjusted to the new UART frequency
2019-10-27 ice40 HX1K: try to access AD9283 ADC with the C code for 6502 with register
2019-10-27 ice40 HX1K: the AD9283 ADC data register is accessable now with the C firmware executed on the 6502 SoftCPU
2019-10-31 Started LP1K firmware
2019-11-03 ice40HX1K capSense board firmware I
2019-11-03 ice40HX1K capSense board fixed errors in the PCB
2019-11-03 ice40HX1K capSense copypaste
2019-11-03 ice40HX1K capSense senses 0??
2019-11-03 ice40HX1K capSense senses 1??
2019-11-03 ice40HX1K capSense senses still zero
2019-11-03 ice40HX1K capSense senses finger with glitches
2019-11-03 ice40HX1K capSense senses 6 buttons
2019-11-10 started new boards
2019-11-14 LEDregul I board
2019-12-23 nRF52 start
2019-12-30 nrf52: production 1
2019-12-30 started LEDboard, THS5641board, ADC08100board
2019-12-30 THS5641, ADC08100, ADC08060 boards
2019-12-31 Oscillator chain board
2020-01-03 started RFboard1; BC547
2020-01-07 more RFboard
2020-01-11 THS5641 DAC output works
2020-01-11 THS5641 DAC output works: UART almost fixed
2020-01-11 ice40HX1K 6502: interrupt is called
2020-01-20 nRF52 board + capSense
2020-01-20 ADC08100 + ice40HX1K works
2020-01-23 RFboard
2020-02-15 firmware flash
2020-02-15 it seems ice40HX1K => AD9283 ADC => THS5641 DAC works (at least it shows values)
2020-02-18 nrf52 modules
2020-02-29 new ice40HX1K SRAM board
2020-03-01 ice40HX1K board next with SRAM AS7C34096A
2020-03-15 fix compilation after GCC update + flash script
2020-03-15 nRF52 module => OM13088 Board UART works
2020-04-20 std MCU board
2020-04-20 std boards skeletons
2020-04-20 std Atmel USB skeletons
2020-04-21 std FPGA skeleton
2020-04-26 std nRF52 skeleton
2020-04-27 some power skeleton
2020-05-01 some esp8266 skeleton
2020-05-03 some power-v1.zip skeleton
2020-05-04 some power3X.pro skeleton
2020-05-04 some charger.kicad_pcb skeleton
2020-05-05 some afe skeleton
2020-05-10 first THS5641board.kicad_pcb revision
2020-05-10 first ADC08100board.kicad_pcb revision
2020-05-15 FPGA HX1K with clock source board test Verilog
2020-05-16 FPGA HX1K try run 6502 with 32 kHz
2020-05-16 more boards skeleton
2020-05-19 M10578-A2 footprint
2020-05-20 M10578-A3 footprint
2020-05-23 GPS board #1
2020-05-23 started Nuvoton N32926 board skeleton
2020-05-23 started Power 12V board skeleton
2020-05-23 started nuvoTon N32926U1DN board skeleton
2020-05-24 started GPS board skeleton
2020-06-20 At least I see some garbage on the UART
2020-06-20 At least I see some Hello World on the UART
2020-06-20 UART RX interrupt works
2020-06-21 UART RX char in C code
2020-06-30 started u-blox GPS CAM-M8Q experiment
2020-06-30 started u-blox GPS CAM-M8Q footpring and spark experiment
2020-07-01 u-blox GPS CAM-M8Q
2020-07-03 periferals
2020-07-15 periferals RLsense
2020-07-17 RLcirc.zip
2020-07-24 Started Electrolyzer board
2020-07-28 opamp for electrolyzer?
2020-07-29 Started Electrolyzer board: sense
2023-07-23 simple version
